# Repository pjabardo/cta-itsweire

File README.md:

# cta-itsweire
Constant temperature anemometers inspired by the 1983 paper by Itsweire and Helloand

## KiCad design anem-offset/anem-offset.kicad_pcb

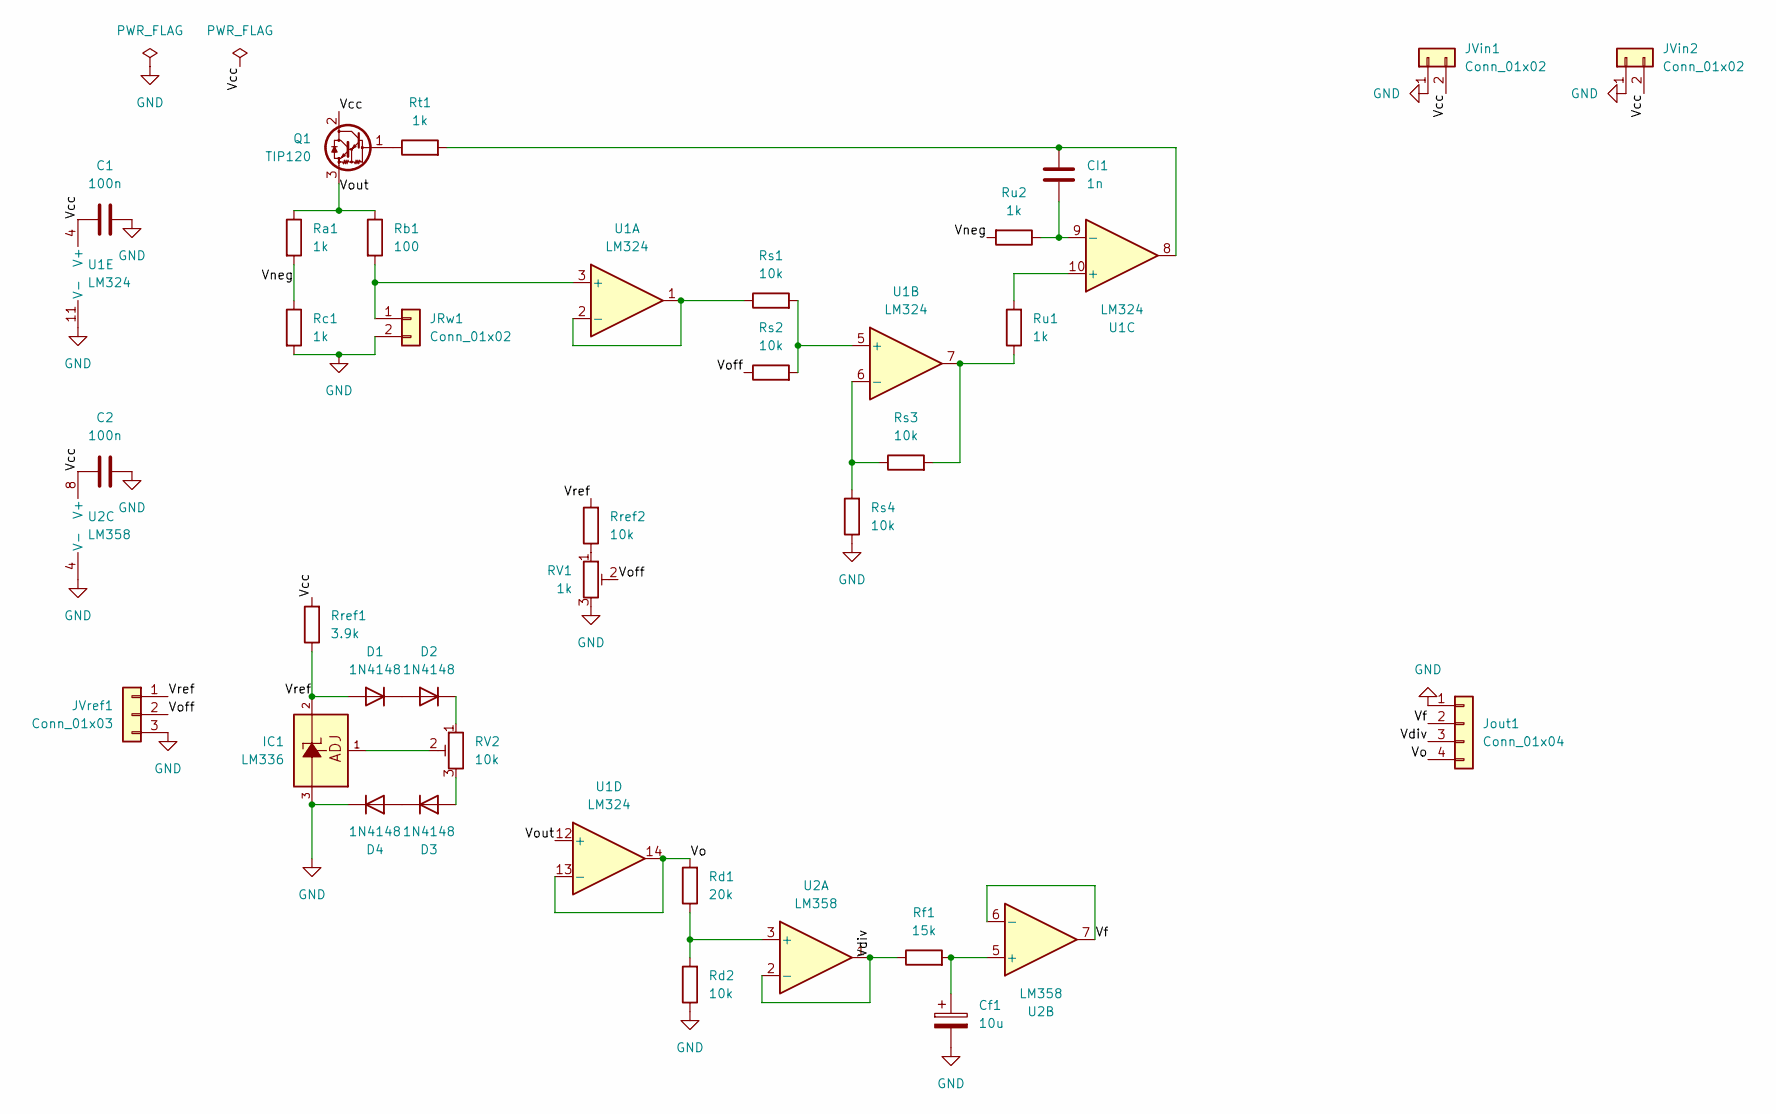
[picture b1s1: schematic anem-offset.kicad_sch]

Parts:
C1, C2: 100n; C_Disc_D5.0mm_W2.5mm_P2.50mm
CI1: 1n; C_Rect_L7.2mm_W3.5mm_P5.00mm_FKS2_FKP2_MKS2_MKP2
Cf1: 10u; CP_Radial_D5.0mm_P2.50mm
D1, D2, D3, D4: 1N4148; D_DO-35_SOD27_P7.62mm_Horizontal
IC1: LM336; TO-92L_Inline_Wide
JRw1: Conn_01x02; PinHeader_1x02_P2.54mm_Vertical
JVin1, JVin2: Conn_01x02; TerminalBlock_Phoenix_MKDS-1,5-2-5.08_1x02_P5.08mm_Horizont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
JVref1: Conn_01x03; PinHeader_1x03_P2.54mm_Vertical
Jout1: Conn_01x04; PinHeader_1x04_P2.54mm_Vertical
Q1: TIP120; TO-220-3_Vertical
RV1: 1k; Potentiometer_Bourns_3296W_Vertical
RV2: 10k; Potentiometer_Bourns_3296W_Vertical
Ra1: 1k; R_Axial_DIN0207_L6.3mm_D2.5mm_P10.16mm_Horizontal
Rb1: 100; R_Axial_DIN0414_L11.9mm_D4.5mm_P15.24mm_Horizontal
Rc1: 1k; R_Axial_DIN0207_L6.3mm_D2.5mm_P10.16mm_Horizontal
Rd1: 20k; R_Axial_DIN0207_L6.3mm_D2.5mm_P10.16mm_Horizontal
Rd2: 10k; R_Axial_DIN0207_L6.3mm_D2.5mm_P10.16mm_Horizontal
Rf1: 15k; R_Axial_DIN0207_L6.3mm_D2.5mm_P10.16mm_Horizontal
Rref1: 3.9k; R_Axial_DIN0207_L6.3mm_D2.5mm_P10.16mm_Horizontal
Rref2: 10k; R_Axial_DIN0207_L6.3mm_D2.5mm_P10.16mm_Horizontal
Rs1, Rs2, Rs3, Rs4: 10k; R_Axial_DIN0207_L6.3mm_D2.5mm_P10.16mm_Horizontal
Rt1: 1k; R_Axial_DIN0207_L6.3mm_D2.5mm_P10.16mm_Horizontal
Ru1, Ru2: 1k; R_Axial_DIN0207_L6.3mm_D2.5mm_P10.16mm_Horizontal
U1: LM324; DIP-14_W7.62mm_LongPads
U2: LM358; DIP-8_W7.62mm_Socket_LongPads

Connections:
/Vcc: C1.1, C2.1, JVin1.2, JVin2.2, Q1.2 (C), Rref1.2, U1.4 (V+), U2.8 (V+)
/Vdiv: Jout1.3, Rf1.1, U2.1, U2.2 (-)
/Vf: Jout1.2, U2.6 (-), U2.7
/Vneg: Ra1.2, Rc1.1, Ru2.2
/Vo: Jout1.4, Rd1.2, U1.13 (-), U1.14
/Voff: JVref1.2, RV1.2, Rs2.1
/Vout: Q1.3 (E), Ra1.1, Rb1.1, U1.12 (+)
/Vref: D1.2 (A), IC1.2, JVref1.1, Rref1.1, Rref2.2
GND: C1.2, C2.2, Cf1.2, D4.1 (K), IC1.3, JRw1.2, JVin1.1, JVin2.1, JVref1.3, Jout1.1, RV1.3, Rc1.2, Rd2.1, Rs4.1, U1.11 (V-), U2.4 (V-)
unnamed: CI1.1, Rt1.2, U1.8
unnamed: D1.1 (K), D2.2 (A)
unnamed: D2.1 (K), RV2.1
unnamed: D3.2 (A), RV2.3
unnamed: D3.1 (K), D4.2 (A)
unnamed: IC1.1, RV2.2
unnamed: JRw1.1, Rb1.2, U1.3 (+)
unnamed: Q1.1 (B), Rt1.1
unnamed: RV1.1, Rref2.1
unnamed: Rs3.2, Ru1.1, U1.7
unnamed: Rs1.1, U1.1, U1.2 (-)
unnamed: Rs1.2, Rs2.2, U1.5 (+)
unnamed: Rs3.1, Rs4.2, U1.6 (-)
unnamed: Ru1.2, U1.10 (+)
unnamed: CI1.2, Ru2.1, U1.9 (-)
unnamed: Rd1.1, Rd2.2, U2.3 (+)
unnamed: Cf1.1, Rf1.2, U2.5 (+)

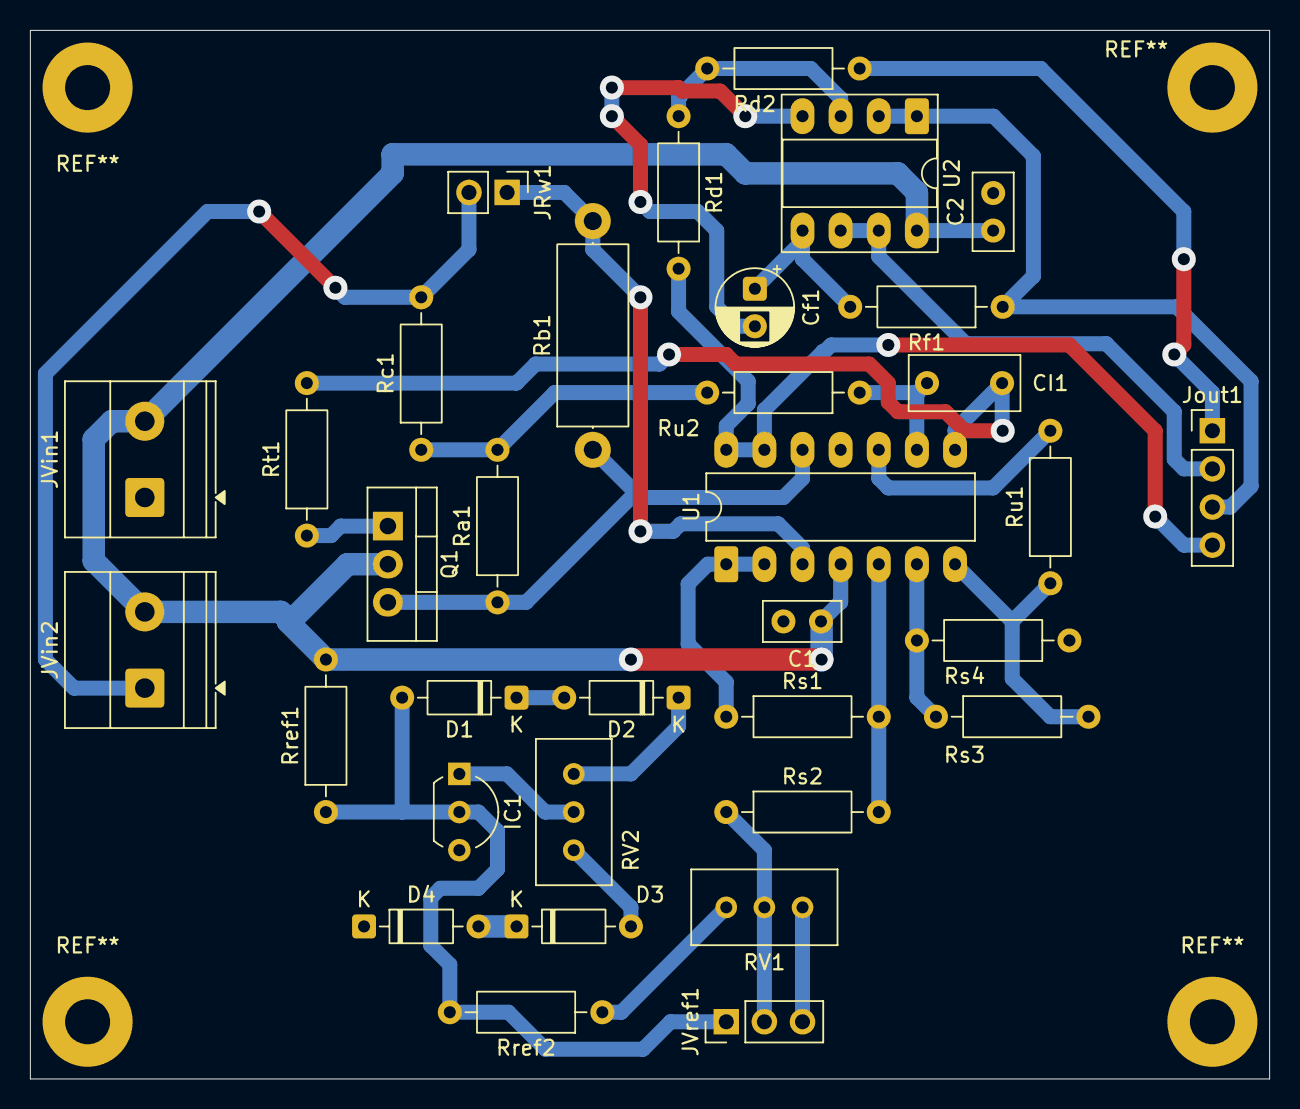
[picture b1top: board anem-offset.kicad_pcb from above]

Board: 2 copper layers, 82.5 x 69.8 mm, 34 parts (0 on the bottom side), 26 nets.

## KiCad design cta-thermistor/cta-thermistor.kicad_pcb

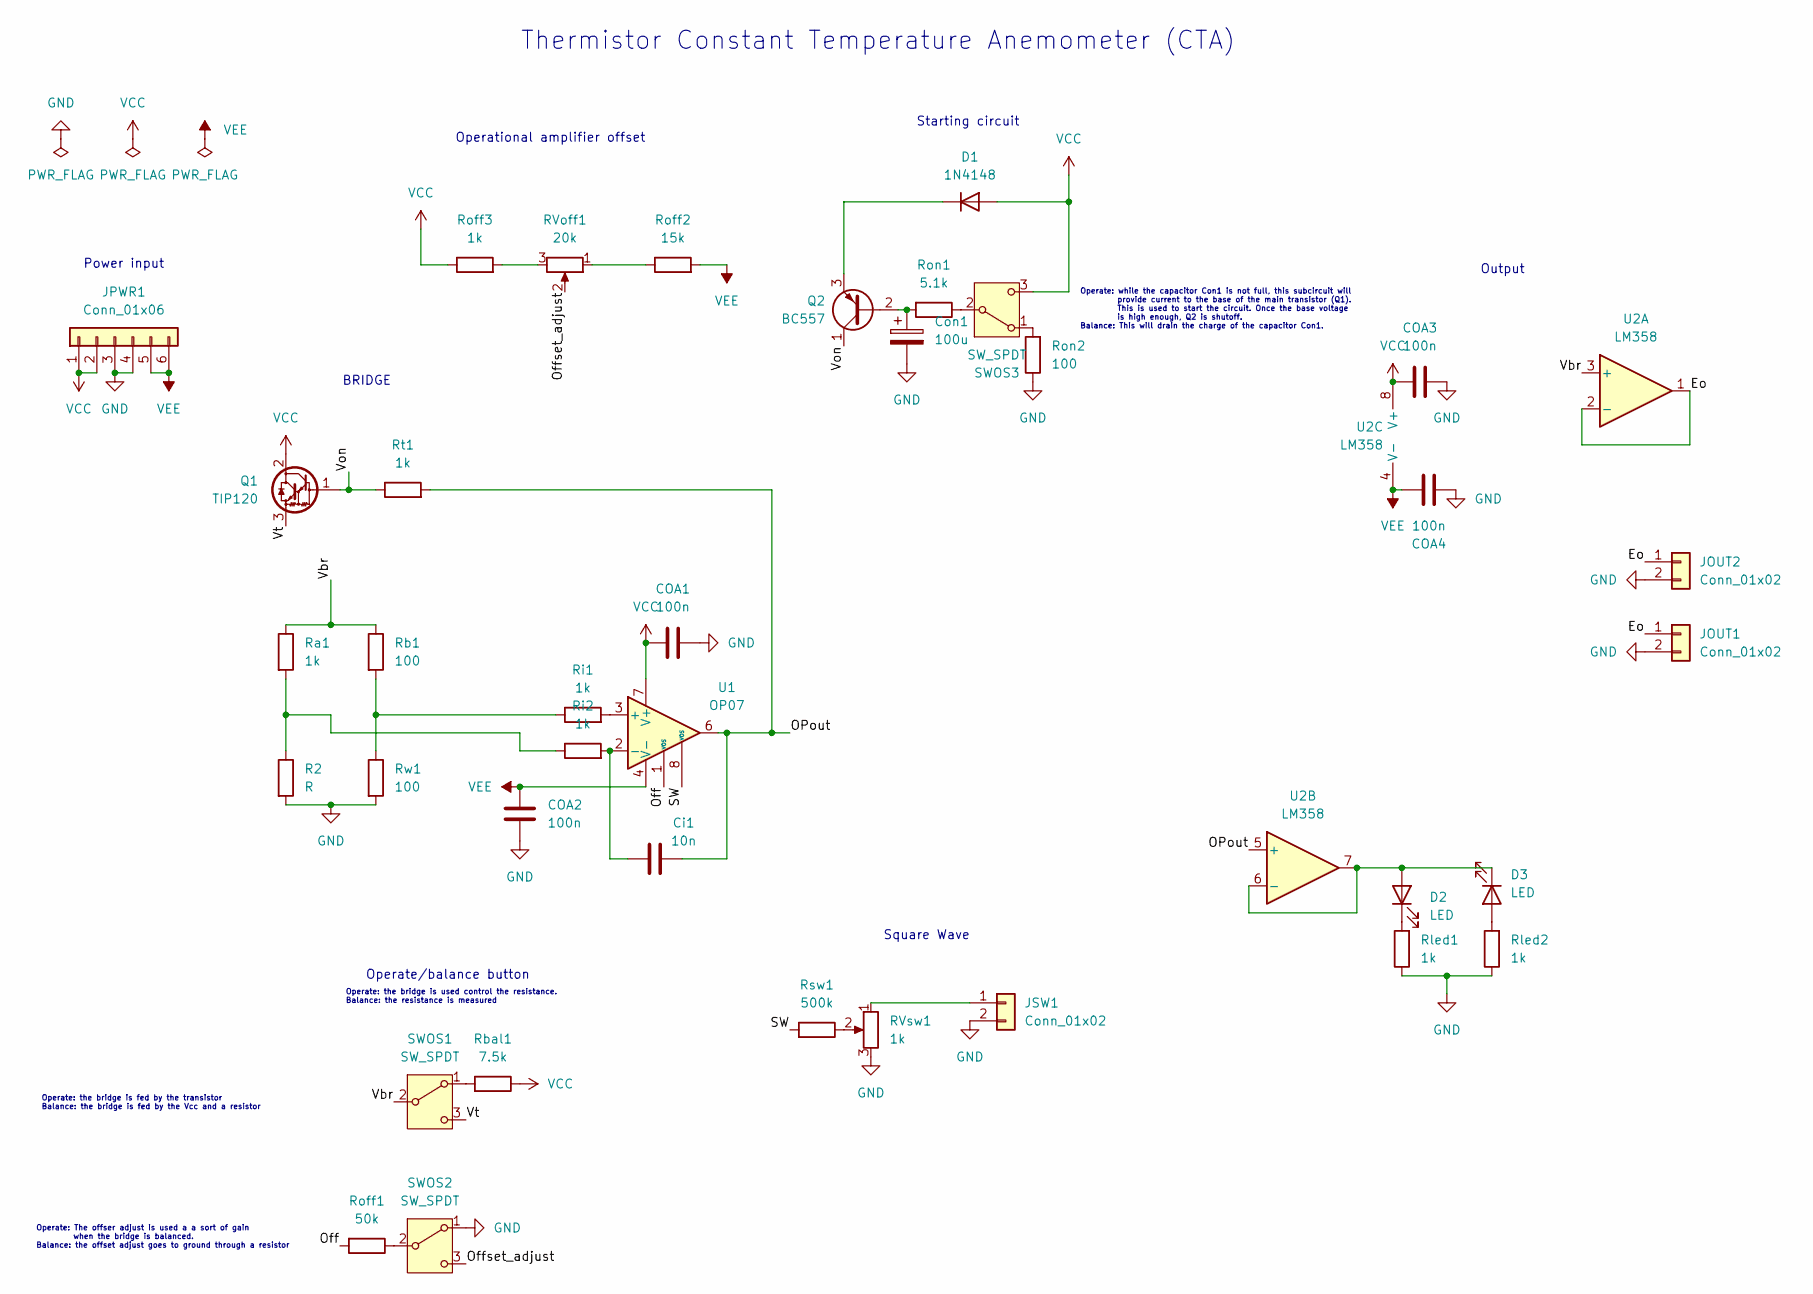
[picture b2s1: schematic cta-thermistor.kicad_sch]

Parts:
COA1, COA2, COA3, COA4: 100n; C_Disc_D3.8mm_W2.6mm_P2.50mm
Ci1: 10n; C_Rect_L7.0mm_W3.5mm_P5.00mm
Con1: 100u; CP_Radial_D8.0mm_P3.50mm
D1: 1N4148; D_DO-35_SOD27_P7.62mm_Horizontal
D2, D3: LED; LED_D3.0mm
JOUT1: Conn_01x02; TerminalBlock_bornier-2_P5.08mm
JOUT2: Conn_01x02; PinHeader_1x02_P2.54mm_Vertical
JPWR1: Conn_01x06; TerminalBlock_bornier-6_P5.08mm
JSW1: Conn_01x02; TerminalBlock_bornier-2_P5.08mm
Q1: TIP120; TO-220-3_Vertical
Q2: BC557; TO-92_Inline_Wide
R2: R; R_Axial_DIN0207_L6.3mm_D2.5mm_P7.62mm_Horizontal
RVoff1: 20k; Potentiometer_Bourns_3296W_Vertical
RVsw1: 1k; Potentiometer_Bourns_3296W_Vertical
Ra1: 1k; R_Axial_DIN0207_L6.3mm_D2.5mm_P7.62mm_Horizontal
Rb1: 100; R_Axial_DIN0414_L11.9mm_D4.5mm_P15.24mm_Horizontal
Rbal1: 7.5k; R_Axial_DIN0207_L6.3mm_D2.5mm_P7.62mm_Horizontal
Ri1, Ri2: 1k; R_Axial_DIN0207_L6.3mm_D2.5mm_P7.62mm_Horizontal
Rled1, Rled2: 1k; R_Axial_DIN0207_L6.3mm_D2.5mm_P7.62mm_Horizontal
Roff1: 50k; R_Axial_DIN0207_L6.3mm_D2.5mm_P7.62mm_Horizontal
Roff2: 15k; R_Axial_DIN0207_L6.3mm_D2.5mm_P7.62mm_Horizontal
Roff3: 1k; R_Axial_DIN0207_L6.3mm_D2.5mm_P7.62mm_Horizontal
Ron1: 5.1k; R_Axial_DIN0207_L6.3mm_D2.5mm_P7.62mm_Horizontal
Ron2: 100; R_Axial_DIN0207_L6.3mm_D2.5mm_P7.62mm_Horizontal
Rsw1: 500k; R_Axial_DIN0207_L6.3mm_D2.5mm_P7.62mm_Horizontal
Rt1: 1k; R_Axial_DIN0207_L6.3mm_D2.5mm_P7.62mm_Horizontal
Rw1: 100; TerminalBlock_bornier-2_P5.08mm
SWOS1, SWOS2, SWOS3: SW_SPDT; PinHeader_1x03_P2.54mm_Vertical
U1: OP07; DIP-8_W7.62mm_LongPads
U2: LM358; DIP-8_W7.62mm_LongPads

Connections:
/Eo: JOUT1.1, JOUT2.1, U2.1, U2.2 (-)
/OPout: Ci1.2, Rt1.2, U1.6, U2.5 (+)
/Off: Roff1.2, U1.1 (VOS)
/Offset_adjust: RVoff1.2, SWOS2.3 (C)
/SW: Rsw1.2, U1.8 (VOS)
/Vbr: Ra1.1, Rb1.1, SWOS1.2 (B), U2.3 (+)
/Von: Q1.1 (B), Q2.1 (C), Rt1.1
/Vt: Q1.3 (E), SWOS1.3 (C)
GND: COA1.1, COA2.1, COA3.1, COA4.1, Con1.2, JOUT1.2, JOUT2.2, JPWR1.3, JPWR1.4, JSW1.2, R2.2, RVsw1.3, Rled1.1, Rled2.1, Ron2.1, Rw1.2, SWOS2.1 (A)
unnamed: D1.1 (K), Q2.3 (E)
unnamed: D2.2 (A), D3.1 (K), U2.6 (-), U2.7
unnamed: D2.1 (K), Rled1.2
unnamed: D3.2 (A), Rled2.2
unnamed: JSW1.1, RVsw1.1
unnamed: Con1.1, Q2.2 (B), Ron1.2
unnamed: R2.1, Ra1.2, Ri2.1
unnamed: RVoff1.1, Roff2.1
unnamed: RVoff1.3, Roff3.2
unnamed: RVsw1.2, Rsw1.1
unnamed: Rb1.2, Ri1.1, Rw1.1
unnamed: Rbal1.2, SWOS1.1 (A)
unnamed: Roff1.1, SWOS2.2 (B)
unnamed: Ron2.2, SWOS3.1 (A)
unnamed: Ron1.1, SWOS3.2 (B)
unnamed: Ri1.2, U1.3 (+)
unnamed: Ci1.1, Ri2.2, U1.2 (-)
VCC: COA1.2, COA3.2, D1.2 (A), JPWR1.1, JPWR1.2, Q1.2 (C), Rbal1.1, Roff3.1, SWOS3.3 (C), U1.7 (V+), U2.8 (V+)
VEE: COA2.2, COA4.2, JPWR1.5, JPWR1.6, Roff2.2, U1.4 (V-), U2.4 (V-)

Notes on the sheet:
BRIDGE
Operate: The offser adjust is used a a sort of gain when the bridge is balanced. Balance: the offset adjust goes to ground through a resistor
Starting circuit
Output
Power input
Operate: while the capacitor Con1 is not full, this subcircuit will provide current to the base of the main transistor (Q1). This is used to start the circuit. Once the base voltage is high enough, Q2 is shutoff. Balance: This will drain the charge of the capacitor Con1.
Operational amplifier offset
Thermistor Constant Temperature Anemometer (CTA)
Operate: the bridge is used control the resistance. Balance: the resistance is measured
Square Wave
Operate/balance button
Operate: the bridge is fed by the transistor Balance: the bridge is fed by the Vcc and a resistor

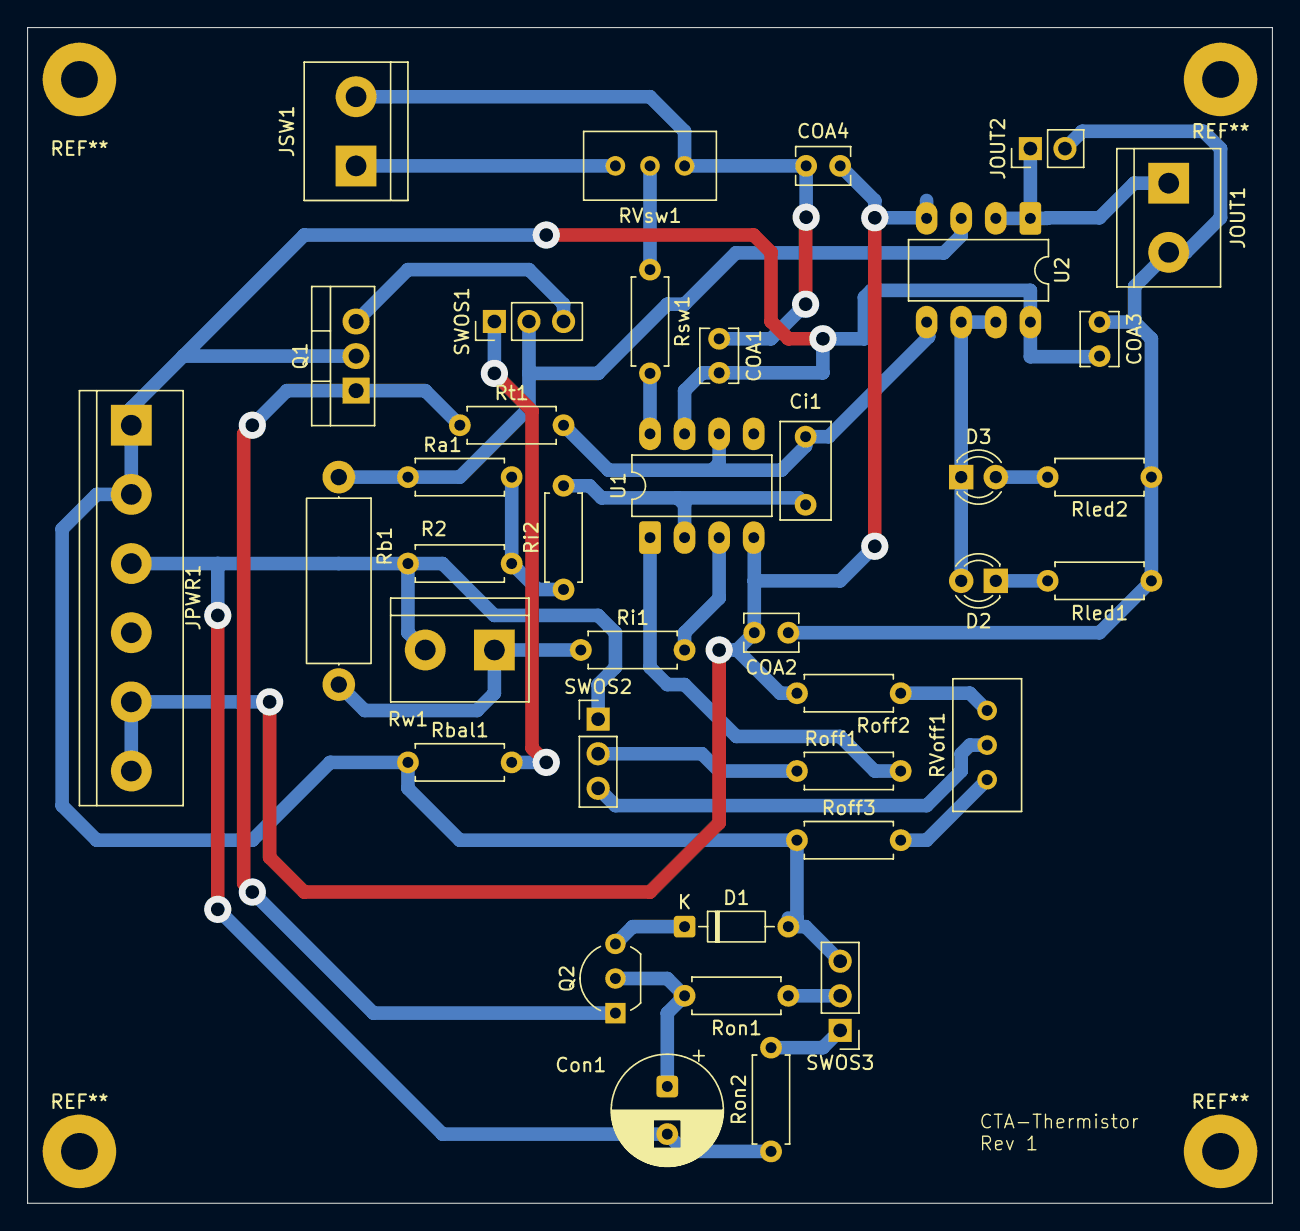
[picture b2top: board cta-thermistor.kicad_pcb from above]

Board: 2 copper layers, 91.4 x 86.4 mm, 38 parts (0 on the bottom side), 28 nets.

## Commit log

2025-08-03 First board for NTC thermistors
    I reproduced the ideas from the paper but for NTC thermistors.
2025-08-03 Small change. A via was on a PTH resistor
    Not wrong but kind of annoying when you are making the PCB by hand.
2025-08-09 I used the wrong footprint for the OpAmps
    I mistakenly selected a wide footprint. Used the opportunity to do some improvements on the PCB layout.
2025-08-09 Created new silk screens and images
    I need to build these things...
2025-09-22 Created a new circuit: anem-offset
    Instead of using the offser adjust pins, we now add an external voltage.
2025-09-23 Pequenas correções e melhorias
    * Furos de montagem
    * Valores 'mais corretos' dos componentes.
